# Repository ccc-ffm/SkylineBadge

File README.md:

# SkylineBadge
See https://wiki.ccc-ffm.de/projekte:skyline_badge:start?&#benoetigte_software for details

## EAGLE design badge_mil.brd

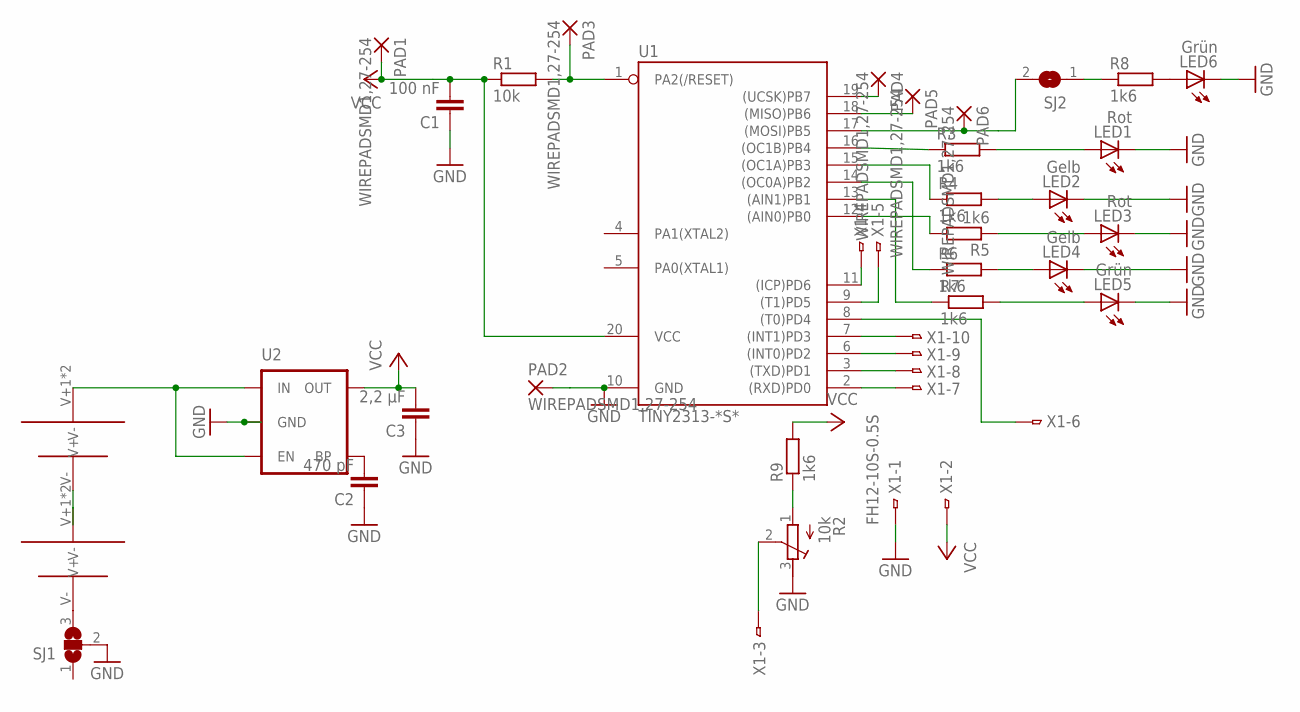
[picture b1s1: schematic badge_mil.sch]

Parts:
C1: 100 nF; C0805
C2: 470 pF; C0805
C3: 2,2 µF; C0805
LED1, LED3: Rot; SML0603
LED2, LED4: Gelb; SML0603
LED5, LED6: Grün; SML0603
PAD1, PAD2, PAD3, PAD4, PAD5, PAD6: WIREPADSMD1,27-254; SMD1,27-2,54
R1: 10k; R0805
R2: 10k; RTRIM4G/J
R3, R4, R5, R6, R7, R8, R9: 1k6; R0805
SJ1: SJ2WW; SJ_2W
SJ2: SJW
U1: TINY2313-*S*; SO20L$
U2: MIC52055V; SOT23-5
U$1, U$2: KEYSTONE3002
X1: FH12-10S-0.5S; FH12-10S-1.0SH

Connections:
GND: C1.1, C2.1, C3.1, LED1.C, LED2.C, LED3.C, LED4.C, LED5.C, LED6.C, PAD2.1, R2.3 (A), SJ1.2, U1.10 (GND), U2.2 (GND), X1.1
unnamed: PAD3.1, R1.2, U1.1 (PA2(/RESET))
unnamed: PAD5.1, U1.18 ((MISO)PB6)
unnamed: PAD6.1, SJ2.2, U1.17 ((MOSI)PB5)
unnamed: PAD4.1, U1.19 ((UCSK)PB7)
unnamed: LED6.A, R8.2
unnamed: LED5.A, R7.2
unnamed: LED4.A, R6.2
unnamed: U$1.V-, U$2.V+1 (V+), U$2.V+2 (V+)
unnamed: LED1.A, R3.2
unnamed: R3.1, U1.16 ((OC1B)PB4)
unnamed: R4.1, U1.15 ((OC1A)PB3)
unnamed: R6.1, U1.14 ((OC0A)PB2)
unnamed: R7.1, U1.13 ((AIN1)PB1)
unnamed: U1.2 ((RXD)PD0), X1.7
unnamed: U1.3 ((TXD)PD1), X1.8
unnamed: U1.6 ((INT0)PD2), X1.9
unnamed: U1.7 ((INT1)PD3), X1.10
unnamed: U1.8 ((T0)PD4), X1.6
unnamed: U1.9 ((T1)PD5), X1.5
unnamed: U1.11 ((ICP)PD6), X1.4
unnamed: R2.1 (E), R9.1
unnamed: SJ1.3, U$2.V-
unnamed: R8.1, SJ2.1
unnamed: C2.2, U2.4 (BP)
unnamed: U2.1 (IN), U2.3 (EN), U$1.V+1 (V+), U$1.V+2 (V+)
unnamed: LED2.A, R4.2
unnamed: LED3.A, R5.1
unnamed: R5.2, U1.12 ((AIN0)PB0)
unnamed: R2.2 (S), X1.3
VCC: C1.2, C3.2, PAD1.1, R1.1, R9.2, U1.20 (VCC), U2.5 (OUT), X1.2

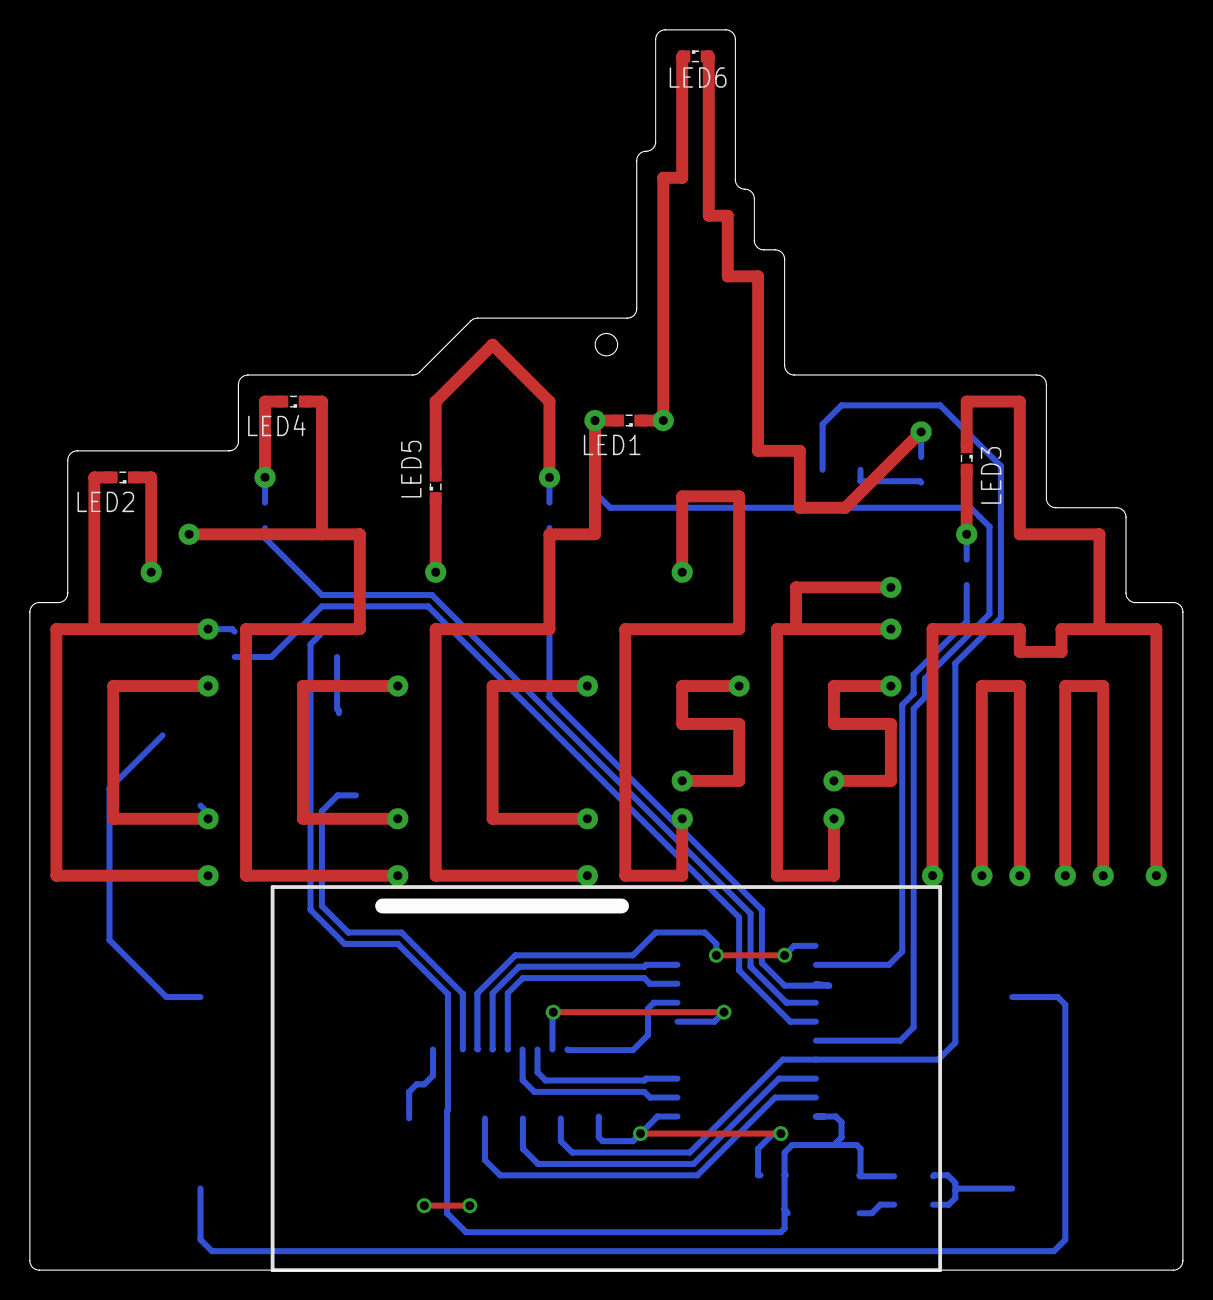
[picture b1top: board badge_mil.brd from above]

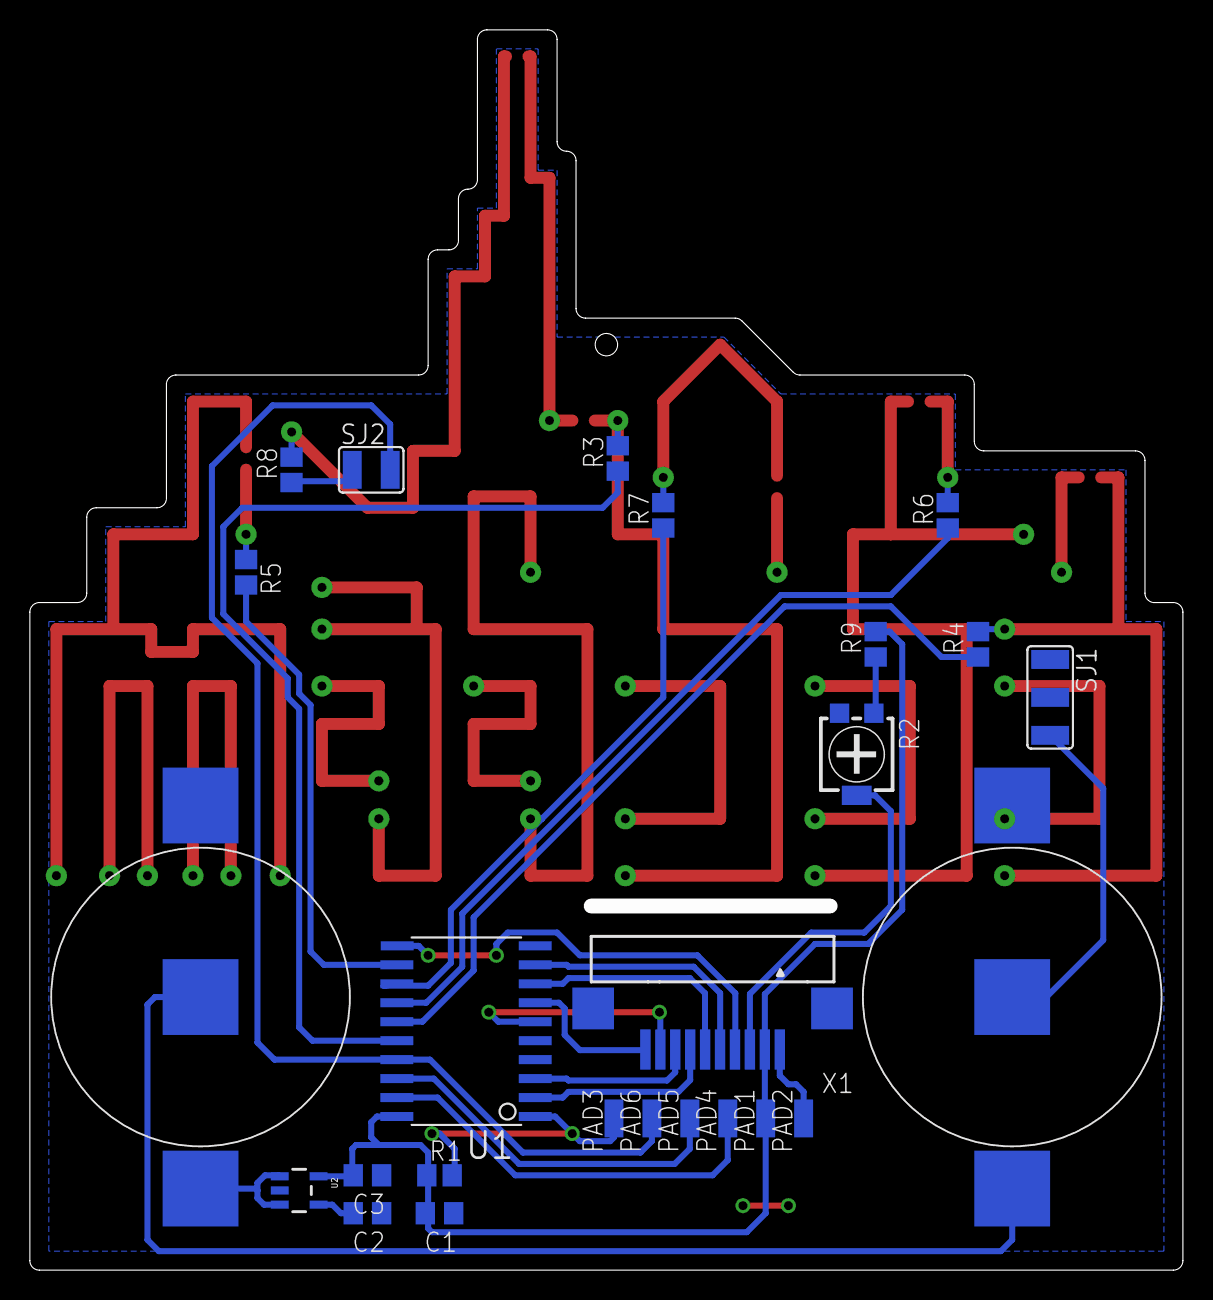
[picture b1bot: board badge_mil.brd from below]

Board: 2 copper layers, 76.2 x 82.1 mm, 31 parts (25 on the bottom side), 31 nets.

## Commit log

2015-01-16 Layout
2015-01-16 Layout fix
2015-01-16 adjust everything, change border
2015-01-16 fix airwire
2015-01-16 small details
2015-01-16 move via out of sight
2015-01-21 add via like in original logo
2015-01-21 change tStop layer
2015-01-21 Resistor Package
2015-01-21 optimize ground plane
2015-01-22 Added jumper as power switch
2015-01-22 LCD contrast poti
2015-01-22 smash LED6
2015-01-22 Minor changes
2015-01-22 straighten wire
2015-01-22 correct merge
2015-01-22 redesign, add render scripts
2015-01-23 fix short circuit, optimize minor things
2015-01-23 little things
2015-01-23 minor tweaks
2015-02-01 MIC5205 for power supply
2015-02-02 fix short circuit
2015-03-23 Testfirmware
2015-03-23 Comments, Cleanup
2015-03-23 Moved eagle files to eagle/
2015-03-23 Ignore local toolpath dir
2015-03-23 Blank TOOL_PATH
2015-03-23 Add Board
2015-03-23 ignore local datasheets dir
2015-03-23 ignore local parts dir
2015-03-24 Add imagef of board and schematic
2015-03-24 Final firmware
2015-03-27 Move hole
2015-03-27 Minor fixes
2015-03-27 Add link
2015-03-29 Test shift_left
2015-03-30 Ignore IDE stuff
2015-03-30 Update TOOL_PATH
2015-03-30 Add scrolling
2015-03-30 cleanup
2015-03-30 Add shift routines
2015-03-30 Ignore local folder
2015-03-30 Add Makefile
2015-03-30 Firmware for hardware test
2015-04-17 Minor adjustments for production

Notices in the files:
parts and their libraries:
SparkFun-PowerIC: Licensing: Creative Commons ShareAlike 4.0 International - https://creativecommons.org/licenses/by-sa/4.0
